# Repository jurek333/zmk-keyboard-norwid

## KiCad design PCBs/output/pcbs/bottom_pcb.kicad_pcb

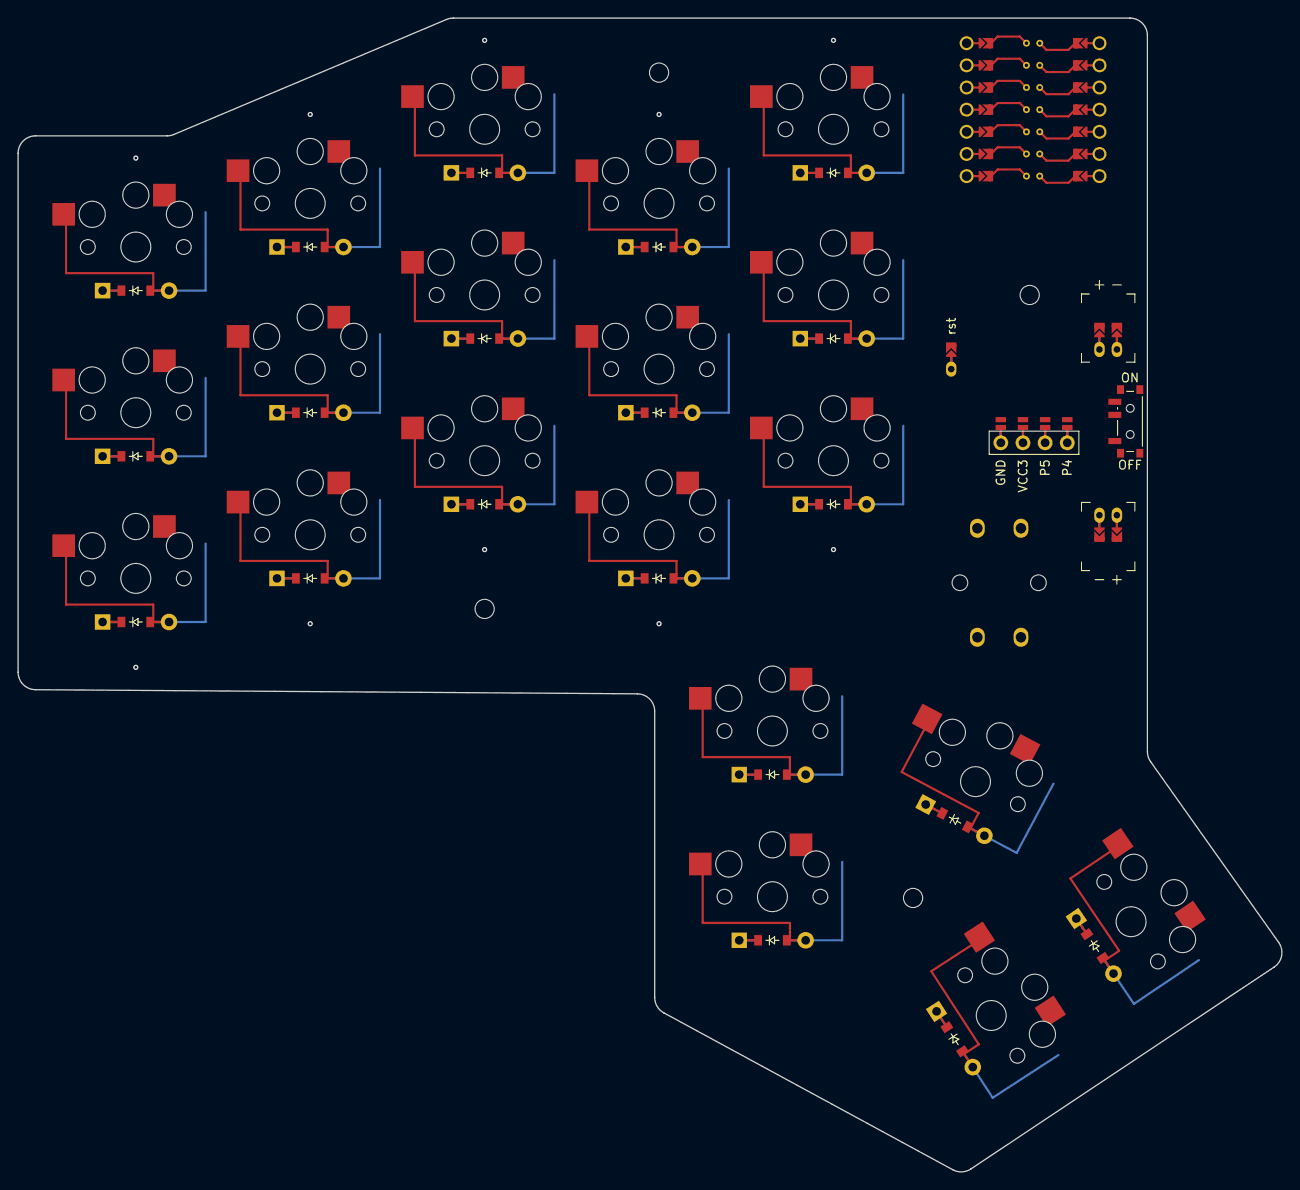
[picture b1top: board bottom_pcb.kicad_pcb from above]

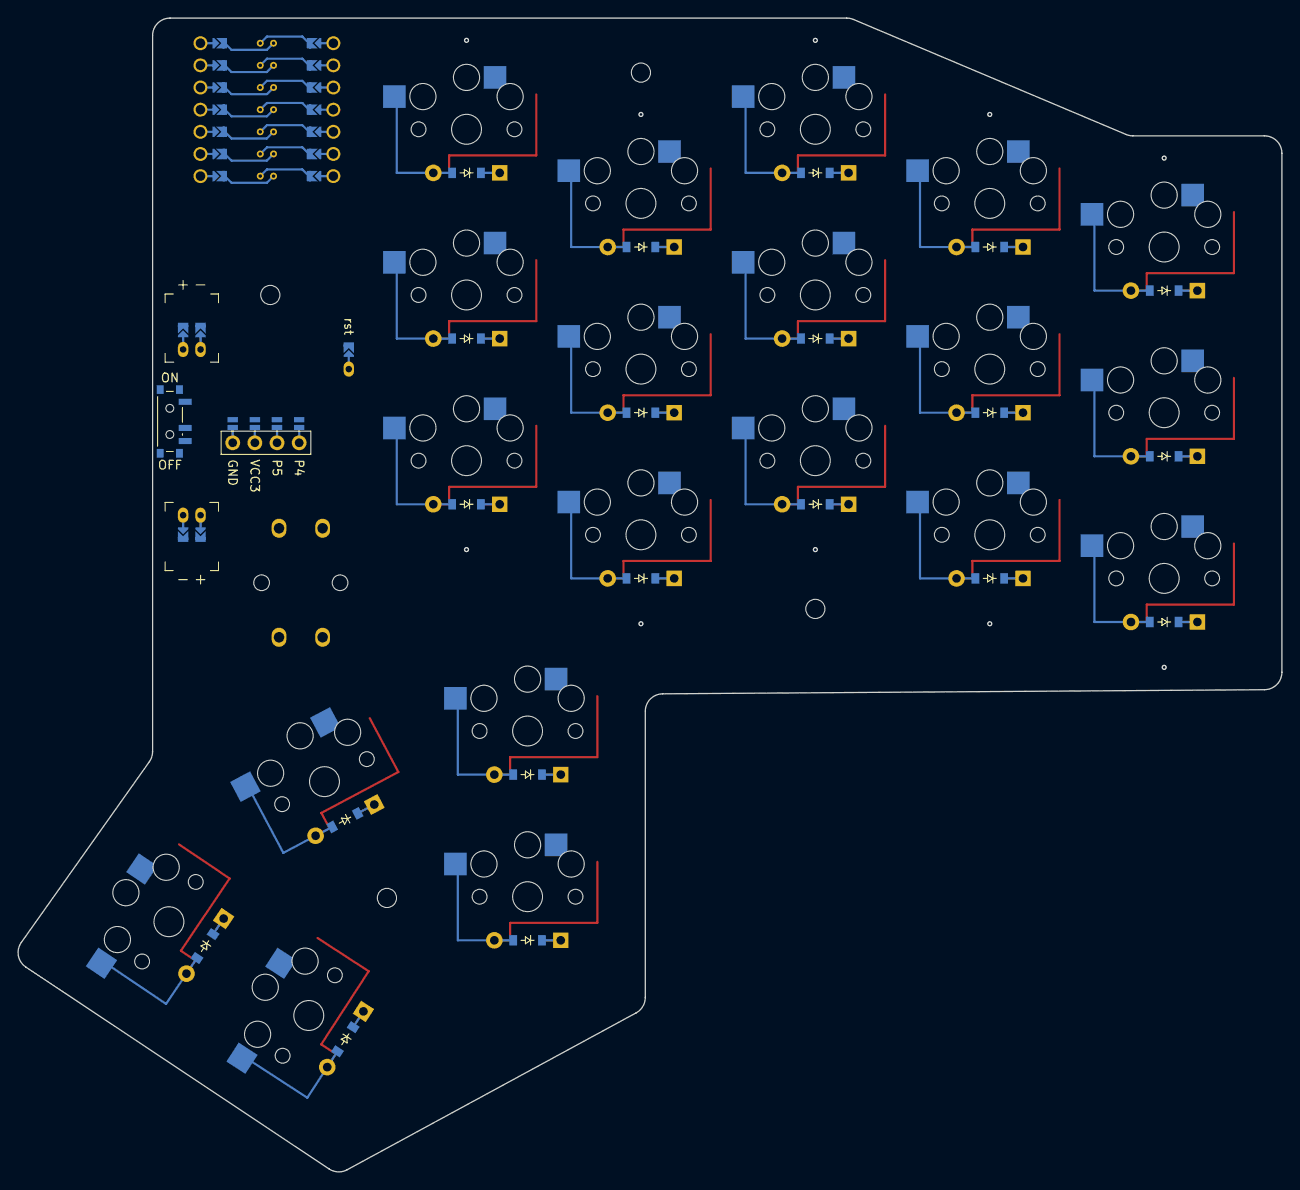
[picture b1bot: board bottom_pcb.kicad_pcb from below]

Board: 2 copper layers, 144.9 x 132.3 mm, 51 parts (2 on the bottom side), 46 nets.

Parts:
D1, D2, D3, D4, D5, D6, D7, D8, D9, D10, D11, D12, D13, D14, D15, D16, D17, D18, D19, D20: ComboDiode
DISP1: display_ssd1306
JST1, JST2: battery_connector_jst_ph_2
MH1, MH2, MH3, MH4: mounting_hole_npth
PIN1: pin
PWR1: power_switch_smd_side
S1, S2, S3, S4, S5, S6, S7, S8, S9, S10, S11, S12, S13, S14, S15, S16, S17, S18, S19, S20: PG1350
S21: OMRON_B3F-4055
xiao-ble1: ProMicro; xiao-ble

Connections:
BAT_N: JST1.2, JST2.2
BAT_P: JST1.1, PWR1.2
DISP1_1: DISP1.1, DISP1.10, DISP1.23
DISP1_2: DISP1.2, DISP1.11, DISP1.22
DISP1_3: DISP1.3, DISP1.12, DISP1.21
DISP1_4: DISP1.4, DISP1.13, DISP1.20
GND: DISP1.14, DISP1.24, S21.1, S21.2, xiao-ble1.23
JST1_1: JST1.11, JST1.21, JST1.31
JST1_2: JST1.12, JST1.22, JST1.32
JST2_1: JST2.11, JST2.21, JST2.31
JST2_2: JST2.12, JST2.22, JST2.32
MCU_BAT_P: JST2.1, PWR1.1, PWR1.3
P0: D3.1, D6.1, D9.1, D12.1, D15.1, xiao-ble1.1
P1: D2.1, D5.1, D8.1, D11.1, D14.1, xiao-ble1.2
P2: D1.1, D4.1, D7.1, D10.1, D13.1, xiao-ble1.3
P3: D16.1, D17.1, D18.1, D19.1, D20.1, xiao-ble1.4
P4: DISP1.17, DISP1.27, xiao-ble1.5
P5: DISP1.16, DISP1.26, xiao-ble1.6
P6: S13.1, S14.1, S15.1, S18.1, xiao-ble1.7
P7: S10.1, S11.1, S12.1, S17.1, xiao-ble1.18
P8: S7.1, S8.1, S9.1, S16.1, xiao-ble1.19
P9: S4.1, S5.1, S6.1, S19.1, xiao-ble1.20
P10: S1.1, S2.1, S3.1, S20.1, xiao-ble1.21
PIN1_1: PIN1.11, PIN1.21, PIN1.31
RST: PIN1.1, S21.3, S21.4
VCC3: DISP1.15, DISP1.25, xiao-ble1.22
far_thumb: D18.2, S18.2
far_thumbLow: D20.2, S20.2
home_thumb: D17.2, S17.2
home_thumbLow: D19.2, S19.2
index_bottom: D10.2, S10.2
index_home: D11.2, S11.2
index_top: D12.2, S12.2
inner_bottom: D13.2, S13.2
inner_home: D14.2, S14.2
inner_top: D15.2, S15.2
middle_bottom: D7.2, S7.2
middle_home: D8.2, S8.2
middle_top: D9.2, S9.2
near_thumb: D16.2, S16.2
pinky_bottom: D1.2, S1.2
pinky_home: D2.2, S2.2
pinky_top: D3.2, S3.2
ring_bottom: D4.2, S4.2
ring_home: D5.2, S5.2
ring_top: D6.2, S6.2

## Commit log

2025-08-14 try to config module for new shield
2025-08-14 build yaml
2025-08-14 fixes icluding of missing file
2025-08-14 adds keymap
2025-08-14 fixes keymap
2025-08-14 fix kaymap
2025-08-20 ads PCB automate ocb
2025-08-25 firmware - displayon
2025-08-25 firmware - display on - fixes
2025-08-25 fix 2
2025-08-25 missing param
2025-08-25 toggle
2025-08-25 fix outref
2025-08-25 move to config
2025-08-25 oled without thread
2025-08-25 defconfig
2025-08-25 oled in yml
2025-08-26 external oled adapter
2025-08-26 oled
2025-08-26 xhanges to propoer xiao
2025-08-26 turn off oled external adapter
2025-08-26 oled i2c conf
2025-08-26 try nice_oled
2025-08-26 try adapter one more time
2025-08-26 change res
2025-08-26 switch to dongle
2025-08-26 wpm off
2025-08-26 turn off wpm in system for right
2025-08-30 work on case
2025-09-01 layout
2025-09-01 mods - include
2025-09-01 fix bt keymapping
2025-09-01 unused including
2025-09-02 right without lcd, remove translation
2025-09-02 add better transform - simplest
2025-09-02 remove lcd from right
2025-09-03 Update norwid.keymap
    Add DQT (double quote) to symbol layer, minus to alpha layer instead on SQT (single quote)
2025-09-03 newwer case, fixed keymap - navigation on layers + better arrows
2025-09-03 new case
2025-09-03 try something new with lcd
2025-09-03 fix?
2025-09-03 swith widgets
2025-09-03 turn off modifiers frm lcd
2025-09-04 fix bad usb socket
2025-09-05 timeless home-row mods
2025-09-05 fix key-positions
    norwid has 40 keys
2025-09-05 change thumb navigation - switch places
2025-09-05 hefty stands
2025-09-05 add transformation and new behaviors + reorganization of directions and PG/HOME/END
2025-09-05 fix keymap
2025-09-07 names for layers
2025-09-07 fix a typo
2025-09-08 replace layer keys
2025-09-08 last fix to replacing layer switches
2025-09-08 fix 2 typos
2025-09-08 thumb optimization
2025-09-08 change lay order
2025-09-09 for vs navi
2025-09-16 move del and bckspc
2025-09-17 silent_norwid with nice!View
2025-09-17 silent_norwid with nice!View - fix
2025-09-17 change buffer
2025-09-18 silent left
2025-09-18 turn off turning off display on idle
2025-09-25 stace and backspace replaced
2025-09-30 bspc and del moved
2025-10-10 sharp mem
2025-10-10 sharp mem p.3
2025-10-10 sharp mem p.4
2025-10-10 sharp mem p.5
2025-10-10 sharp mem p.6
2025-10-10 sharp mem p.7
2025-10-10 move oled section from right to left
2025-10-10 turn off explicite Word count
2025-10-10 remve adapter
2025-10-10 change sharp reg
2025-10-11 define LV configs
2025-10-11 revert - define LV configs
2025-10-11 try to fix nice nano
2025-10-11 try to fix nice nano - p2
2025-10-11 try to fix nice nano - p4
2025-10-12 split - move nice lsc to another board/shield
2025-10-12 change gpio use
2025-10-12 remove if_enabled
2025-10-12 reverse -44
2025-10-12 remove requires from nice norwid
2025-10-12 cleanup?
2025-10-30 fix numerical dot
2025-11-05 nice norwid
2025-11-06 bad ampersend
2025-11-06 return to prev
2026-02-03 fix - maybe for silend_norwid
2026-02-03 try to fix norwid left
2026-02-04 set proper version
2026-02-04 new mapping
2026-02-04 fix comma in numers
2026-02-04 cmakelists 4 view
2026-02-04 screen code
2026-02-04 bad lvgl
2026-02-04 screen
2026-02-05 revert changes
2026-02-05 reverted changes - t line emoved again
2026-02-05 remove all statuses from screen
2026-02-05 off - nicenano
2026-02-05 silent without screen for now - a way to separate shilds
2026-02-05 little cleanup of configuration
2026-02-05 silent with and without lcd
2026-02-06 turn on some lcd nfo
2026-02-06 turn on some lcd info
2026-02-06 mask some code
2026-02-06 only inits-no drawings
2026-03-02 simplify to max LCD widget
2026-03-02 remove default shield config
2026-03-02 sharp does not define cs-gpio
2026-03-02 bad comments
2026-03-02 missing lvgl
2026-03-02 fixes macro usage
2026-03-02 fixes missing include
2026-03-02 fix to fix
2026-03-02 Rename display_mj_init to mj_initchange names so it not collide
2026-03-02 remove what is not needed
2026-03-02 change font size
2026-03-02 change font size part 2
